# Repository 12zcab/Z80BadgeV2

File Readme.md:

# Z80 Badge V2

## a total redesign of my fallout badge!

## submitted to Gadget@HackClub

# HUGE THXXXX to Cyao and Acon and mpk for suggestions!!!!

### Images

### What is this?

its a small Z80 Computer with 32kByte of EEPROM and 32kByte of SRAM.
it have a minimum setup with practical IO components like LCD1602 and Buttons

Programming this device require you to burn a custom-OS of it or use Dupont Wire to connect its IO PinHeaders to a EEPROM programmer while pausing the whole device and power off.

### How to solder it?

1. Solder EEPROM and SRAM and Chip Select Logics also the 104 capacitors with Reflow or Manual Soldering.
2. Bent the socket's pins and Solder DIP40 Socket and All Resistors.
3. Solder switches and all Buttons and the Crystal OSC.
4. Solder the IO Pin Headers if u want!
5. Solder the 1602 LCD and Plug in all the ICs.
6. Solder the Battery Module and Stick it onto the back of Z80 PIO IC if u need it, Otherwise u can just power with Dupont Wires connecting to the Pin Headers
7. Solder the Battery and Stick it onto the back of Z80 CPU IC if u need it

for BOM details please refer to BOM.csv.

Feel free to open a Issue on GitHub or DM HackClub Slack @12zcab.

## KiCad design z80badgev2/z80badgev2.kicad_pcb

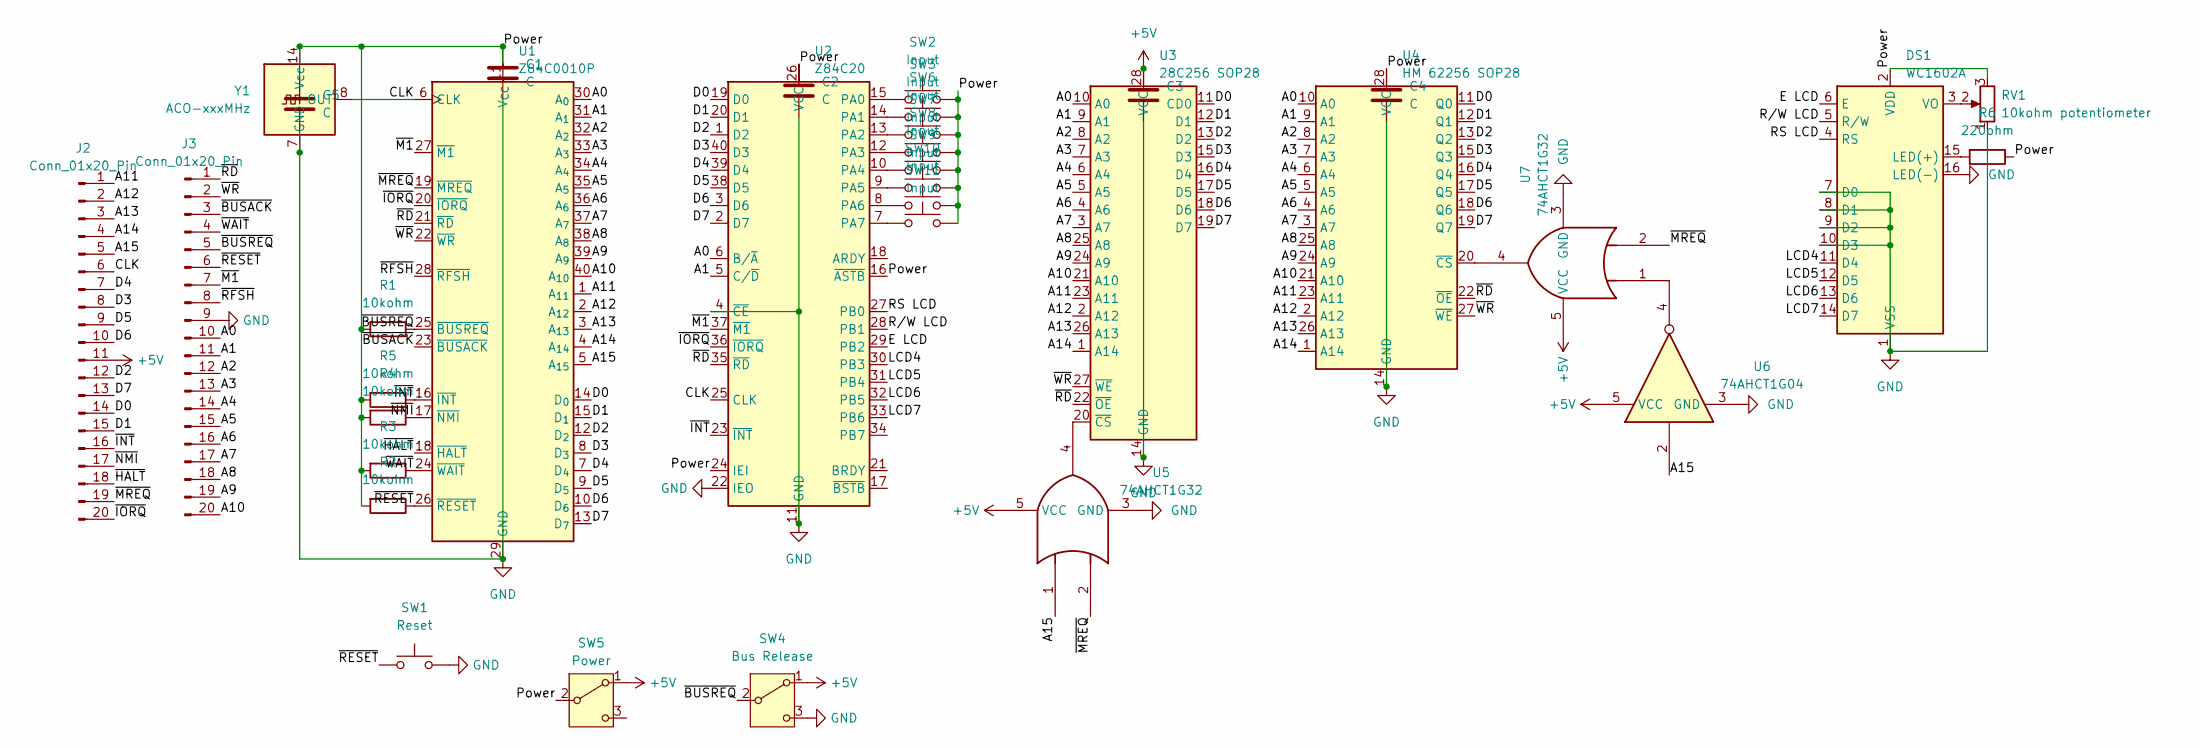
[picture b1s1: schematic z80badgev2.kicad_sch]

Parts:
C1, C2, C3, C4, C5: C; C_0805_2012Metric
DS1: WC1602A
J2, J3: Conn_01x20_Pin; PinHeader_1x20_P2.54mm_Vertical
R1, R2, R3, R4, R5: 10kohm; R_Axial_DIN0207_L6.3mm_D2.5mm_P7.62mm_Horizontal
R6: 220ohm; R_Axial_DIN0207_L6.3mm_D2.5mm_P7.62mm_Horizontal
RV1: 10kohm potentiometer; Potentiometer_Runtron_RM-065_Vertical
SW1: Reset; SW_PUSH_6mm
SW2, SW3, SW6, SW7, SW8, SW9, SW10, SW11: Input; SW_PUSH_6mm
SW4: Bus Release; SW_Slide_SPDT_Straight_CK_OS102011MS2Q
SW5: Power; SW_Slide_SPDT_Straight_CK_OS102011MS2Q
U1: Z84C0010P; SMDIP-40_W15.24mm
U2: Z84C20; SMDIP-40_W15.24mm
U3: 28C256 SOP28; SOP-28_8.4x18.16mm_P1.27mm
U4: HM 62256 SOP28; SOP-28_8.4x18.16mm_P1.27mm
U5, U7: 74AHCT1G32; SOT-23-5_HandSoldering
U6: 74AHCT1G04; SOT-23-5_HandSoldering
Y1: ACO-xxxMHz; Oscillator_DIP-14

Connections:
+5V: C3.2, J2.11, SW4.1 (A), SW5.1 (A), U3.28 (VCC), U5.5 (VCC), U6.5 (VCC), U7.5 (VCC)
/A0: J3.10, U1.30 (A_{0}), U2.6 (B/~A), U3.10 (A0), U4.10 (A0)
/A1: J3.11, U1.31 (A_{1}), U2.5 (C/~D), U3.9 (A1), U4.9 (A1)
/A2: J3.12, U1.32 (A_{2}), U3.8 (A2), U4.8 (A2)
/A3: J3.13, U1.33 (A_{3}), U3.7 (A3), U4.7 (A3)
/A4: J3.14, U1.34 (A_{4}), U3.6 (A4), U4.6 (A4)
/A5: J3.15, U1.35 (A_{5}), U3.5 (A5), U4.5 (A5)
/A6: J3.16, U1.36 (A_{6}), U3.4 (A6), U4.4 (A6)
/A7: J3.17, U1.37 (A_{7}), U3.3 (A7), U4.3 (A7)
/A8: J3.18, U1.38 (A_{8}), U3.25 (A8), U4.25 (A8)
/A9: J3.19, U1.39 (A_{9}), U3.24 (A9), U4.24 (A9)
/A10: J3.20, U1.40 (A_{10}), U3.21 (A10), U4.21 (A10)
/A11: J2.1, U1.1 (A_{11}), U3.23 (A11), U4.23 (A11)
/A12: J2.2, U1.2 (A_{12}), U3.2 (A12), U4.2 (A12)
/A13: J2.3, U1.3 (A_{13}), U3.26 (A13), U4.26 (A13)
/A14: J2.4, U1.4 (A_{14}), U3.1 (A14), U4.1 (A14)
/A15: J2.5, U1.5 (A_{15}), U5.1, U6.2
/CLK: J2.6, U1.6 (CLK), U2.25 (CLK), Y1.8 (OUT)
/D0: J2.14, U1.14 (D_{0}), U2.19 (D0), U3.11 (D0), U4.11 (Q0)
/D1: J2.15, U1.15 (D_{1}), U2.20 (D1), U3.12 (D1), U4.12 (Q1)
/D2: J2.12, U1.12 (D_{2}), U2.1 (D2), U3.13 (D2), U4.13 (Q2)
/D3: J2.8, U1.8 (D_{3}), U2.40 (D3), U3.15 (D3), U4.15 (Q3)
/D4: J2.7, U1.7 (D_{4}), U2.39 (D4), U3.16 (D4), U4.16 (Q4)
/D5: J2.9, U1.9 (D_{5}), U2.38 (D5), U3.17 (D5), U4.17 (Q5)
/D6: J2.10, U1.10 (D_{6}), U2.3 (D6), U3.18 (D6), U4.18 (Q6)
/D7: J2.13, U1.13 (D_{7}), U2.2 (D7), U3.19 (D7), U4.19 (Q7)
/E LCD: DS1.6 (E), U2.29 (PB2)
/LCD4: DS1.11 (D4), U2.30 (PB3)
/LCD5: DS1.12 (D5), U2.31 (PB4)
/LCD6: DS1.13 (D6), U2.32 (PB5)
/LCD7: DS1.14 (D7), U2.33 (PB6)
/Power: C1.2, C2.2, C4.2, C5.2, DS1.2 (VDD), R1.2, R2.2, R3.2, R4.2, R5.2, R6.1, RV1.3, SW2.2, SW3.2, SW5.2 (B), SW6.2, SW7.2, SW8.2, SW9.2, SW10.2, SW11.2, U1.11 (V_{CC}), U2.16 (~ASTB), U2.24 (IEI), U2.26 (VCC), U4.28 (VCC), Y1.14 (Vcc)
/RS LCD: DS1.4 (RS), U2.27 (PB0)
/R/W LCD: DS1.5 (R/W), U2.28 (PB1)
/~BUSACK: J3.3, U1.23 (~BUSACK)
/~BUSREQ: J3.5, R1.1, SW4.2 (B), U1.25 (~BUSREQ)
/~HALT: J2.18, U1.18 (~HALT)
/~INT: J2.16, R5.1, U1.16 (~INT), U2.23 (~INT)
/~IORQ: J2.20, U1.20 (~IORQ), U2.36 (~IORQ)
/~M1: J3.7, U1.27 (~M1), U2.37 (~M1)
/~MREQ: J2.19, U1.19 (~MREQ), U5.2, U7.2
/~NMI: J2.17, R4.1, U1.17 (~NMI)
/~RD: J3.1, U1.21 (~RD), U2.35 (~RD), U3.22 (~OE), U4.22 (~OE)
/~RESET: J3.6, R2.1, SW1.1, U1.26 (~RESET)
/~RFSH: J3.8, U1.28 (~RFSH)
/~WAIT: J3.4, R3.1, U1.24 (~WAIT)
/~WR: J3.2, U1.22 (~WR), U3.27 (~WE), U4.27 (~WE)
GND: C1.1, C2.1, C3.1, C4.1, C5.1, DS1.1 (VSS), DS1.7 (D0), DS1.8 (D1), DS1.9 (D2), DS1.10 (D3), DS1.16 (LED(-)), J3.9, RV1.1, SW1.2, SW4.3 (C), U1.29 (GND), U2.4 (~CE), U2.11 (GND), U2.22 (IEO), U3.14 (GND), U4.14 (GND), U5.3 (GND), U6.3 (GND), U7.3 (GND), Y1.7 (GND)
unnamed: DS1.15 (LED(+)), R6.2
unnamed: DS1.3 (VO), RV1.2
unnamed: SW2.1, U2.15 (PA0)
unnamed: SW3.1, U2.14 (PA1)
unnamed: SW6.1, U2.13 (PA2)
unnamed: SW7.1, U2.12 (PA3)
unnamed: SW8.1, U2.10 (PA4)
unnamed: SW9.1, U2.9 (PA5)
unnamed: SW10.1, U2.8 (PA6)
unnamed: SW11.1, U2.7 (PA7)
unnamed: U3.20 (~CS), U5.4
unnamed: U4.20 (~CS), U7.4
unnamed: U6.4, U7.1

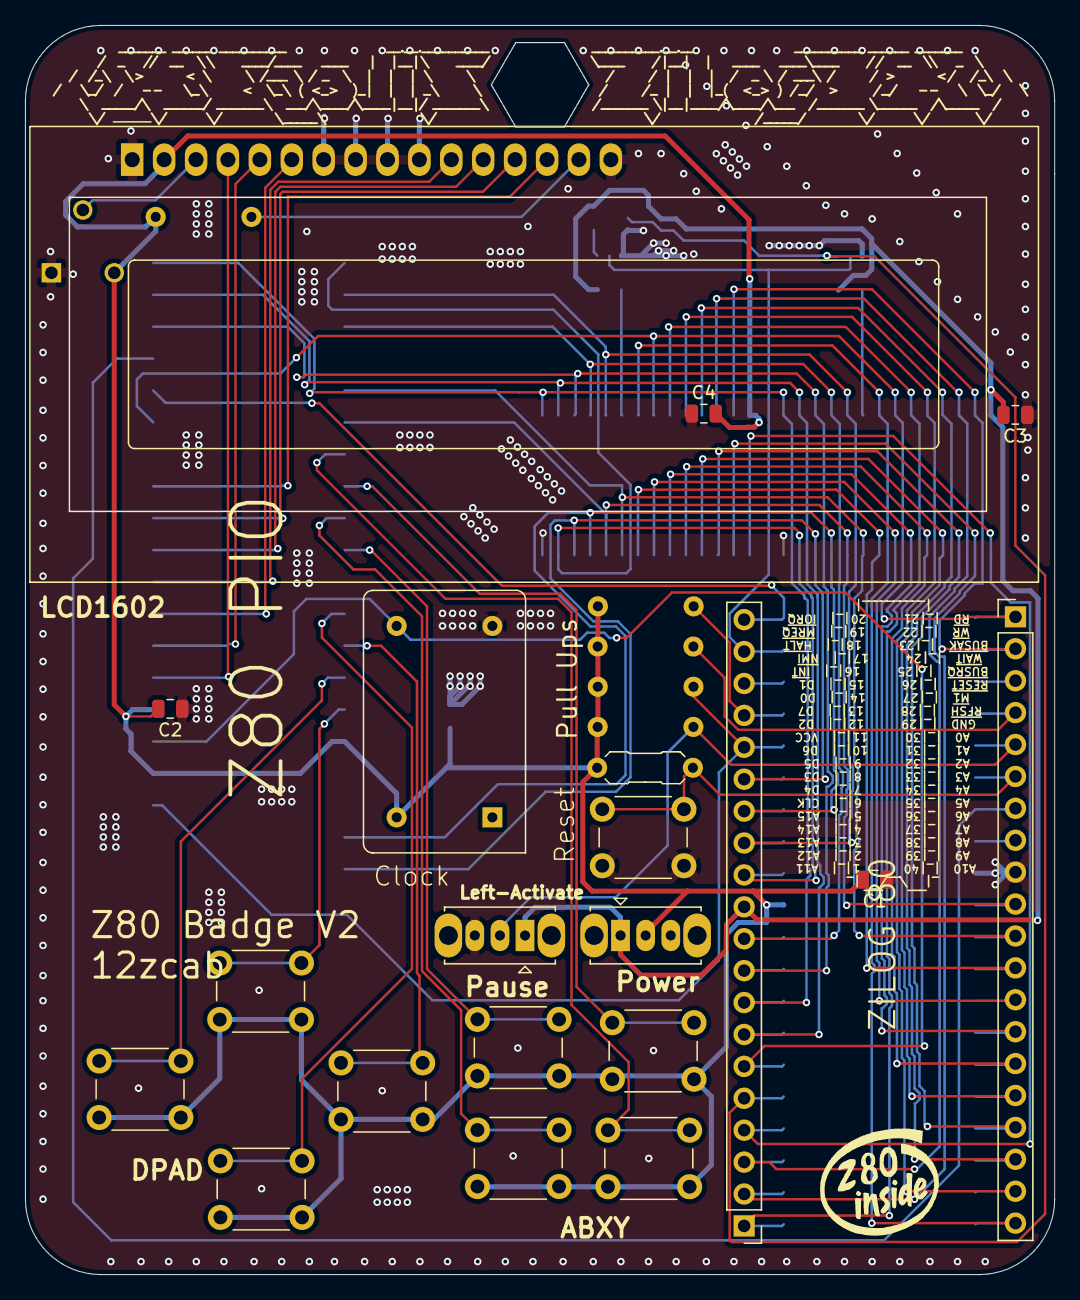
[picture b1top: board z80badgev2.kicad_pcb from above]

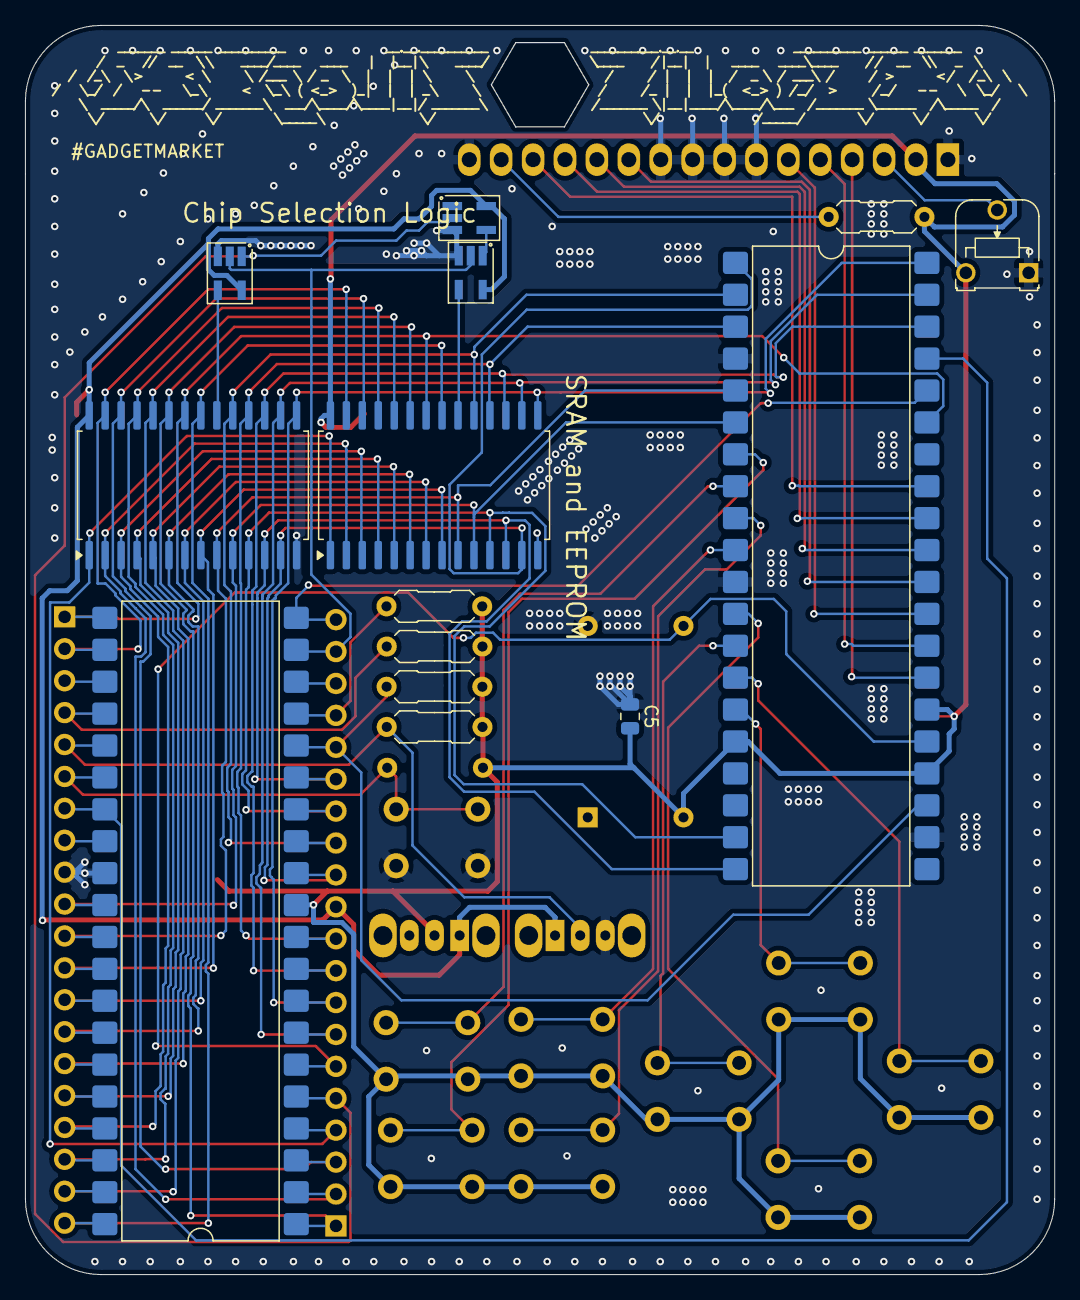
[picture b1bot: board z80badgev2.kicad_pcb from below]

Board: 2 copper layers, 81.9 x 99.4 mm, 34 parts (14 on the bottom side), 61 nets.
